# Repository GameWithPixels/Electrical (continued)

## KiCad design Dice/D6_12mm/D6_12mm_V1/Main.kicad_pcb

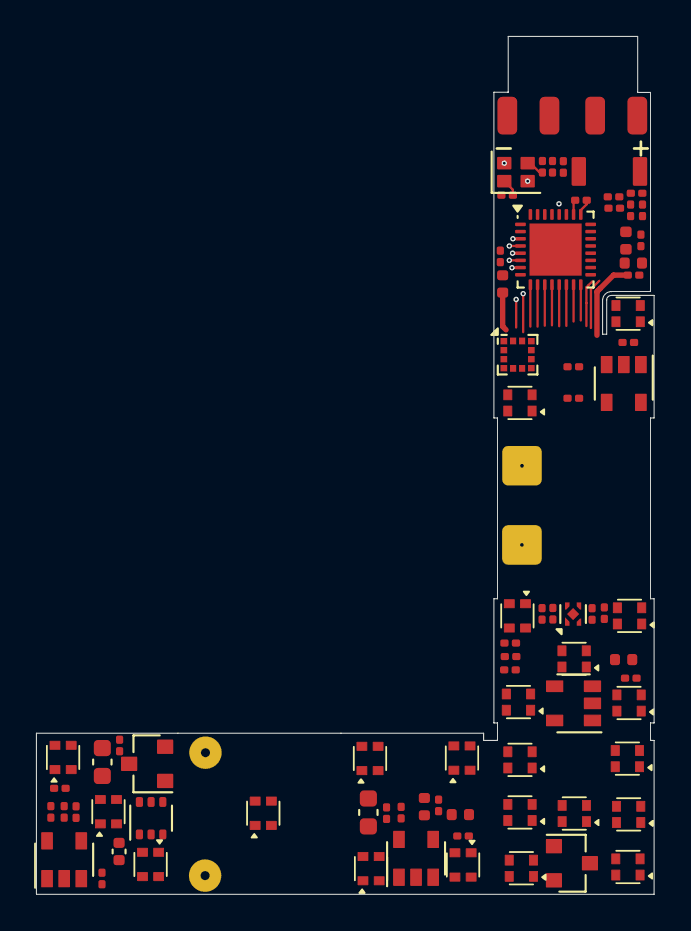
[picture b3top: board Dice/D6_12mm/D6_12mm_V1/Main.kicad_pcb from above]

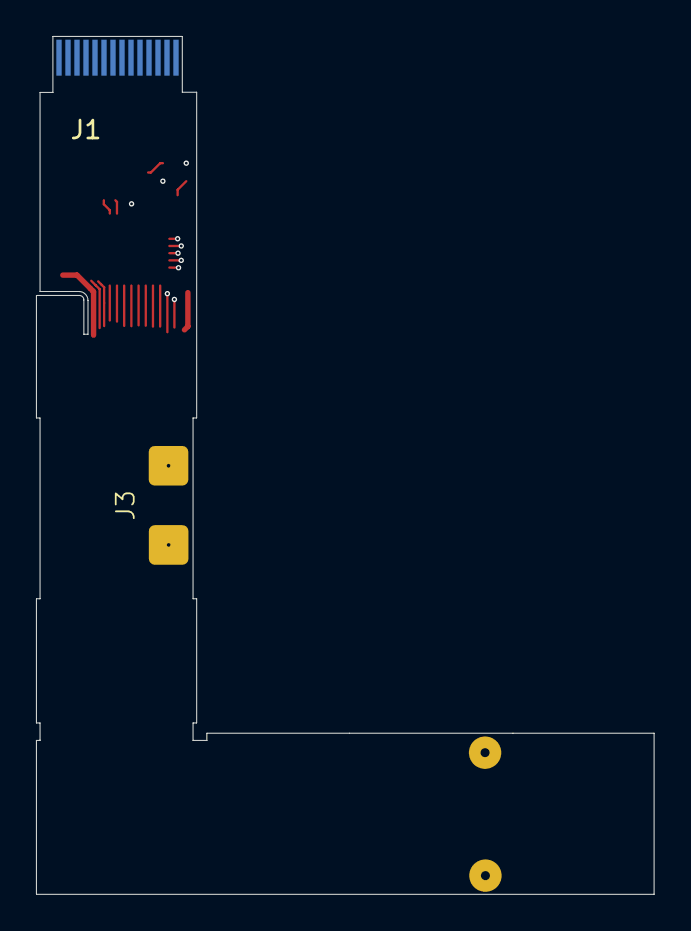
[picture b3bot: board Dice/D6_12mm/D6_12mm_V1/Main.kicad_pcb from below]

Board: 2 copper layers, 34.3 x 47.7 mm, 82 parts (2 on the bottom side), 57 nets.

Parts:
AE1: Antenna_Chip; CHIP_ANT
C1, C9, C10, C18, C29: 4.7uF 10V 20%; C_0402_1005Metric
C2, C5: 12pF 10V 10%; C_0201_0603Metric
C3, C6, C7, C20, C23, C24, C25: 0.1uF 10V 20%; C_0201_0603Metric
C4, C11, C12: DNP; C_0201_0603Metric
C8: 1.2pF 10V 5% C0G; C_0201_0603Metric
C13: 4.7uF 25V 20%; C_0402_1005Metric
C14, C17: 1nF 25V 5% NP0; C_0201_0603Metric
C15: 22uF 10V 20%; C_0603_1608Metric
C19: 10nF 50V 5% NP0; C_0603_1608Metric
C21, C22: 10nF 25V 10%; C_0201_0603Metric
C26, C27, C28: 1.0uF 6.3V 20%; C_0201_0603Metric
D1: BAV99S; SOT-363_SC-70-6
D2, D3, D4, D5, D6, D7, D8, D9, D10, D11, D12, D13, D14, D15, D16, D17, D18, D19, D20, D21, D22, D23: TX1812MWCA5-F01
J1: Conn_01x14; FPC_14
J2: Conn_01x04; FPC-POGO-4
J3: Conn_01x02; Hongjie 10100 Solder Tabs
L1: 2.2uH 10mA 20%; L_0402_1005Metric
L3: 0 Ohm; L_0201_0603Metric
L5: 1.6nH 5%; L_0201_0603Metric
P5: COILA; TestPoint_THTPad_D1.5mm_Drill0.7mm_nosilk
P6: COILB; TestPoint_THTPad_D1.5mm_Drill0.7mm_nosilk
R1, R2, R7: 3.9M 1%; R_0201_0603Metric
R3, R6: R_0201_0603Metric
R4: 10k 1%; R_0201_0603Metric
R8: 10M 1%; R_0201_0603Metric
R9: 100k 1%; R_0201_0603Metric
R10, R11: 3.9k 1%; R_0201_0603Metric
R12: 510R 1%; R_0201_0603Metric
TH1: NTC 100k @ 25C; R_0201_0603Metric
U1: CMT4531; QFN-32-1EP_4x4mm_P0.4mm_EP2.9x2.9mm
U2: SC7A20HTR; LGA-12_2x2mm_P0.5mm
U3: MG78L05AT3; SOT-23
U4: 24C02S(XBLW); SOT-23-5
U5: MT9700; SOT-23-5
U6: ME6212C30M5G; SOT-23-5
U7: DS6101; UDFN-4-1EP_1x1mm_P0.65mm_EP0.48x0.48mm
U8: MGH303A1T3; SOT-23
U9: TP4054(LX); SOT-23-5
Y1: 32MHz 40ppm; Crystal_SMD_2016-4Pin_2.0x1.6mm

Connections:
+5V: C15.1, R1.1, R4.1, U3.1 (VOUT), U9.4 (VCC)
+BATT: C9.1, J3.1, R7.1, R12.1, U5.5 (VIN), U6.1 (VIN), U8.1 (VDD), U9.3 (BAT)
/ACC_INT: U1.13 (PB3), U2.5 (INT1)
/ANTENNA: AE1.1 (FEED), C11.1, L3.2
/ANT_50: C8.1, C12.1, L3.1
/LED_DATA: D2.3 (DIN), U1.4 (PB0)
/LED_RETURN: D23.1 (DOUT), U1.7 (PA6)
/SCL: R10.2, U1.17 (PB7), U2.12 (SCL), U4.1 (SCL)
/SDA: R11.2, U1.16 (PB6), U2.2 (SDA), U4.3 (SDA)
/Wireless Charging/B-: C23.2, J3.2, U7.2 (VSS), U7.5 (PAD)
/Wireless Charging/COILA: C14.1, C17.1, C19.1, D1.3 (K1A2), P5.1
/Wireless Charging/COILB: C14.2, C17.2, C19.2, D1.6 (K3A4), P6.1
/Wireless Charging/COIL_SENSE: C21.1, R1.2, R2.2, U1.9 (PB8)
/Wireless Charging/LED_EN_OUT: U1.12 (PB2), U5.4 (EN)
/Wireless Charging/PROG: R6.1, U1.15 (PB5), U9.5 (PROG)
/Wireless Charging/SM: U1.14 (PB4), U7.3 (SM)
/Wireless Charging/STAT: U1.11 (PB1), U9.1 (CHRG)
/Wireless Charging/TH1: R9.2, TH1.1, U1.18 (PB10)
/Wireless Charging/VBAT_SENSE: C22.1, R7.2, R8.1, U1.10 (PB9)
GND: C1.2, C2.1, C3.2, C4.2, C5.1, C6.2, C7.2, C9.2, C10.2, C11.2, C12.2, C13.2, C15.2, C18.2, C20.2, C21.2, C22.2, C24.2, C25.2, C26.2, C27.2, C28.2, C29.2, D1.1 (A1), D1.4 (A3), D2.2 (GND), D3.2 (GND), D4.2 (GND), D5.2 (GND), D6.2 (GND), D7.2 (GND), D8.2 (GND), D9.2 (GND), D10.2 (GND), D11.2 (GND), D12.2 (GND), D13.2 (GND), D14.2 (GND), D15.2 (GND), D16.2 (GND), D17.2 (GND), D18.2 (GND), D19.2 (GND), D20.2 (GND), D21.2 (GND), D22.2 (GND), D23.2 (GND), J1.3, J1.4, J1.7, J1.8, J2.4, R2.1, R3.2, R4.2, R6.2, R8.2, TH1.2, U1.33 (GND), U2.4 (NC), U2.8 (GND), U2.9 (GND), U3.3 (VSS), U4.2 (GND), U5.2 (GND), U6.2 (VSS), U7.4 (EB-), U8.3 (GND), U9.2 (GND), Y1.2, Y1.4
unnamed: D2.1 (DOUT), D3.3 (DIN)
unnamed: D3.1 (DOUT), D4.3 (DIN)
unnamed: D4.1 (DOUT), D5.3 (DIN)
unnamed: D5.1 (DOUT), D6.3 (DIN)
unnamed: D6.1 (DOUT), D7.3 (DIN)
unnamed: D7.1 (DOUT), D8.3 (DIN)
unnamed: D8.1 (DOUT), D9.3 (DIN)
unnamed: D9.1 (DOUT), D10.3 (DIN)
unnamed: D10.1 (DOUT), D11.3 (DIN)
unnamed: D11.1 (DOUT), D12.3 (DIN)
unnamed: D12.1 (DOUT), D13.3 (DIN)
unnamed: D13.1 (DOUT), D14.3 (DIN)
unnamed: D14.1 (DOUT), D15.3 (DIN)
unnamed: D15.1 (DOUT), D16.3 (DIN)
unnamed: D16.1 (DOUT), D17.3 (DIN)
unnamed: D17.1 (DOUT), D18.3 (DIN)
unnamed: D18.1 (DOUT), D19.3 (DIN)
unnamed: D19.1 (DOUT), D20.3 (DIN)
unnamed: D20.1 (DOUT), D21.3 (DIN)
unnamed: D21.1 (DOUT), D22.3 (DIN)
unnamed: D22.1 (DOUT), D23.3 (DIN)
unnamed: C4.1, C8.2, L5.2, U1.25 (RFIOP)
unnamed: L1.2, U1.23 (SWITCH)
unnamed: C26.1, C27.1, L1.1, U1.24 (VDCDC), U1.27 (VDCDCRF)
unnamed: C1.1, C3.1, U1.8 (VDD_FLASH)
unnamed: L5.1, U1.26 (VDD_PA)
unnamed: C5.2, U1.29 (XO32MM_OUT), Y1.3
unnamed: C2.2, U1.30 (XO32MP_IN), Y1.1
unnamed: R3.1, U5.3 (SET)
unnamed: U6.3 (CE), U8.2 (OUT)
unnamed: C23.1, R12.2, U7.1 (BAT)
RESET: J1.9, U1.3 (RESET)
SWDCLK: J1.6, J2.3, U1.5 (SWDCLK)
SWDIO: J1.5, J2.2, U1.6 (SWDIO)
VDC: C6.1, C10.1, C20.1, C24.1, C25.1, D2.4 (VCC), D3.4 (VCC), D4.4 (VCC), D5.4 (VCC), D6.4 (VCC), D7.4 (VCC), D8.4 (VCC), D9.4 (VCC), D10.4 (VCC), D11.4 (VCC), D12.4 (VCC), D13.4 (VCC), D14.4 (VCC), D15.4 (VCC), D16.4 (VCC), D17.4 (VCC), D18.4 (VCC), D19.4 (VCC), D20.4 (VCC), D21.4 (VCC), D22.4 (VCC), D23.4 (VCC), R9.1, U5.1 (VOUT)
VDD: C7.1, C18.1, C28.1, C29.1, J1.13, J1.14, J2.1, R10.1, R11.1, U1.22 (VCC), U1.28 (VCCRF), U2.3 (IO_VDD), U2.7 (VDD), U4.4 (VCC), U6.5 (VOUT)
VEE: C13.1, D1.2 (K2), D1.5 (K4), U3.2 (VIN)

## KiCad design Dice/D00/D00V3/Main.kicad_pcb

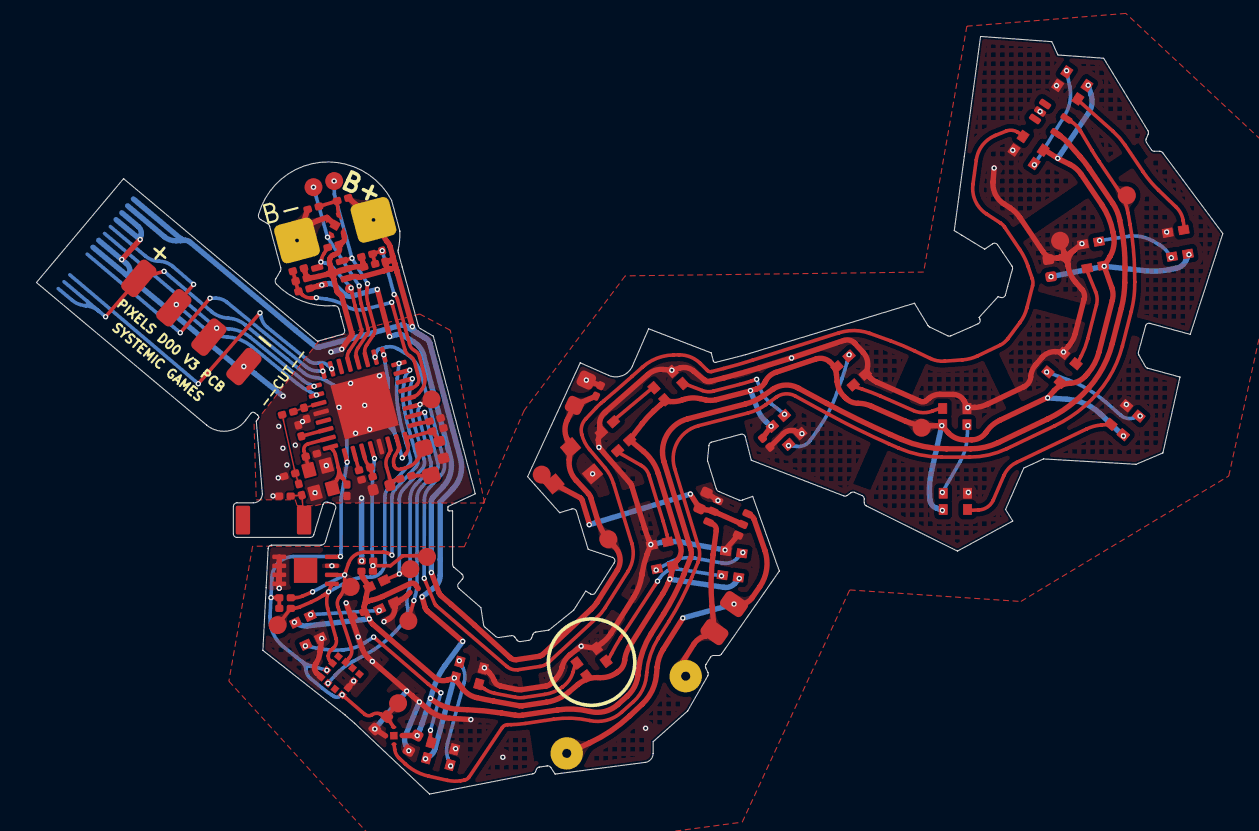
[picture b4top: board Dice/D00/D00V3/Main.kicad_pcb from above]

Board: 2 copper layers, 65.9 x 42.1 mm, 89 parts (1 on the bottom side), 57 nets.

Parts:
AE1: Antenna_Chip; CHIP_ANT
C1, C4, C18: 4.7uF 10V 20%; C_0402_1005Metric
C2, C5: 8pF 10V 10%; C_0201_0603Metric
C3, C6, C10, C14, C23: 0.1uF 10V 20%; C_0201_0603Metric
C7: 100pF NP0 10V 2%; C_0201_0603Metric
C8: 0.8pF 10V 5% C0G; C_0201_0603Metric
C9, C16: 10uF 6.3V 20%; C_0402_1005Metric
C11, C12: DNP; C_0201_0603Metric
C13: 4.7uF 25V 20%; C_0402_1005Metric
C15: 22uF 10V 20%; C_0603_1608Metric
C19: 12nF 50V 5% NP0; C_0805_2012Metric
C21, C22: 10nF 25V 10%; C_0201_0603Metric
D1: BAV99S; SOT-363_SC-70-6
D2, D3, D4, D5, D6, D7, D8, D9, D10, D11, D12, D13, D14, D15, D16, D17, D18, D19, D20: TX1812MWCA5-F01
J1: Conn_01x14; FPC_14
J2: Conn_01x04; FPC-POGO-4
J3: Conn_01x02; Hongjie 10100 Solder Tabs
L1: 10uH 100mA 20%; L_0603_1608Metric
L2: 15nH 100mA 5%; L_0201_0603Metric
L3: 0 Ohm; R_0201_0603Metric
L5: 3.9nH 5%; L_0201_0603Metric
P5: COILA; TestPoint_THTPad_D1.5mm_Drill0.7mm_nosilk
P6: COILB; TestPoint_THTPad_D1.5mm_Drill0.7mm_nosilk
R1, R2, R7: 3.9M 1%; R_0201_0603Metric
R3: 24.3k 1%; R_0201_0603Metric
R4: 10k 1%; R_0201_0603Metric
R5, R9: 100k 1%; R_0201_0603Metric
R6: 3.57k 1%; R_0201_0603Metric
R8: 10M 1%; R_0201_0603Metric
R10, R11: 3.9k 1%; R_0201_0603Metric
R12: 510R 1%; R_0201_0603Metric
TH1: NTC 100k @ 25C; R_0201_0603Metric
U1: N52810_QFN32; QFN-32-1EP_5x5mm_P0.5mm_EP3.1x3.1mm
U2: SC7A20HTR; LGA-12_2x2mm_P0.5mm
U3: PJ75BL50SA; SOT-23
U4: ME6230; FPB1_1-4
U5: BL24C02F-NTRC; TDFN-8-1EP_3x2mm_P0.5mm_EP1.3x1.4mm
U6: AW35122
U7: DS6101; UDFN-4-1EP_1x1mm_P0.65mm_EP0.48x0.48mm
U8: SL1605; SOT-553
U9: XT4051; SOT-553
W1: LED_DATA1; TEST_PIN
W2: PROG; TEST_PIN
W4: VDC; TEST_PIN
W5: SM; TEST_PIN
W6: MAG1; TEST_PIN
W7: ACC_INT; TEST_PIN
W8: SCL; TEST_PIN
W9: SDA; TEST_PIN
W15: +5V; TEST_PIN
W16: VIN; TEST_PIN
W17: STAT; TEST_PIN
W19: GND; TEST_PIN
W20: TH1; TEST_PIN
W21: LED2; TEST_PIN
W25: VDD; TEST_PIN
Y1: 32MHz 40ppm; Crystal_SMD_2016-4Pin_2.0x1.6mm

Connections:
+5V: C15.1, R1.1, R4.1, U3.2 (VOUT), U9.5 (VCC), W15.1
+BATT: C16.1, J1.1, J1.2, J3.1, R7.1, R12.1, U4.4 (VIN), U6.A2 (VIN), U8.4 (VDD), U9.1 (BAT)
/5V_SENSE: C21.1, R1.2, R2.2, U1.5 (P0.05/AIN3)
/ACC_INT: U1.3 (P0.01/XL2), U2.5 (INT1), W7.1
/ANTENNA: AE1.1 (FEED), C11.1, L3.2
/ANT_50: C12.1, L3.1, L5.2
/ANT_NRF: C8.1, L5.1, U1.19 (ANT)
/BATT_NTC_SENSE: R9.2, TH1.1, U1.28 (P0.30/AIN6), W20.1
/LED_DATA: D2.3 (DIN), U1.6 (P0.06), W1.1
/LED_EN: U1.2 (P0.00/XL1), U6.B2 (EN), W21.1
/LED_RETURN: D20.1 (DOUT), U1.10 (P0.12)
/PROG: R6.1, U1.13 (P0.16/TDATA1), U9.4 (PROG), W2.1
/Power Supply/MAG1_: U4.3 (CE), U8.5 (OUT), W6.1
/SCL: R10.2, U1.7 (P0.09), U2.12 (SCL), U5.6 (SCL), W8.1
/SDA: R11.2, U1.8 (P0.10), U2.2 (SDA), U5.5 (SDA), W9.1
/SM: U1.12 (P0.15), U7.3 (SM), W5.1
/STATS: U1.11 (P0.14), U9.3 (CHRG), W17.1
/VBAT_SENSE: C22.1, R7.2, R8.1, U1.4 (P0.04/AIN2)
/Wireless Charging/B-: C23.2, J3.2, U7.2 (VSS), U7.5 (PAD)
/Wireless Charging/COILA: C19.1, D1.3 (K1A2), P5.1
/Wireless Charging/COILB: C19.2, D1.6 (K3A4), P6.1
GND: C1.2, C2.1, C3.2, C4.2, C5.1, C6.2, C7.2, C8.2, C9.2, C10.2, C11.2, C12.2, C13.2, C14.2, C15.2, C16.2, C18.2, C21.2, C22.2, D1.1 (A1), D1.4 (A3), D2.2 (GND), D3.2 (GND), D4.2 (GND), D5.2 (GND), D6.2 (GND), D7.2 (GND), D8.2 (GND), D9.2 (GND), D10.2 (GND), D11.2 (GND), D12.2 (GND), D13.2 (GND), D14.2 (GND), D15.2 (GND), D16.2 (GND), D17.2 (GND), D18.2 (GND), D19.2 (GND), D20.2 (GND), J1.3, J1.4, J1.7, J1.8, J2.4, R2.1, R3.1, R4.2, R6.2, R8.2, TH1.2, U1.20 (VSS), U1.29 (VSS), U1.33 (VSS), U2.4 (NC), U2.8 (GND), U2.9 (GND), U3.1 (VSS), U4.2 (VSS), U5.1 (A0), U5.2 (A1), U5.3 (A2), U5.4 (GND), U5.7 (WP), U6.B1 (GND), U7.4 (EB-), U8.2 (GND), U9.2 (GND), W19.1, Y1.2, Y1.4
unnamed: D2.1 (DOUT), D3.3 (DIN)
unnamed: D3.1 (DOUT), D4.3 (DIN)
unnamed: D4.1 (DOUT), D5.3 (DIN)
unnamed: D5.1 (DOUT), D6.3 (DIN)
unnamed: D6.1 (DOUT), D7.3 (DIN)
unnamed: D7.1 (DOUT), D8.3 (DIN)
unnamed: D8.1 (DOUT), D9.3 (DIN)
unnamed: D9.1 (DOUT), D10.3 (DIN)
unnamed: D10.1 (DOUT), D11.3 (DIN)
unnamed: D11.1 (DOUT), D12.3 (DIN)
unnamed: D12.1 (DOUT), D13.3 (DIN)
unnamed: D13.1 (DOUT), D14.3 (DIN)
unnamed: D14.1 (DOUT), D15.3 (DIN)
unnamed: D15.1 (DOUT), D16.3 (DIN)
unnamed: D16.1 (DOUT), D17.3 (DIN)
unnamed: D17.1 (DOUT), D18.3 (DIN)
unnamed: D18.1 (DOUT), D19.3 (DIN)
unnamed: D19.1 (DOUT), D20.3 (DIN)
unnamed: L1.2, L2.1
unnamed: L1.1, U1.31 (DCC)
unnamed: C3.1, U1.1 (DEC1)
unnamed: C7.1, U1.22 (DEC3)
unnamed: C1.1, L2.2, U1.30 (DEC4)
unnamed: R5.2, U1.26 (P0.25)
unnamed: R3.2, R5.1, U1.27 (P0.28/AIN4)
unnamed: C5.2, U1.23 (XC1), Y1.3
unnamed: C2.2, U1.24 (XC2), Y1.1
unnamed: C23.1, R12.2, U7.1 (BAT)
RESET: J1.9, U1.16 (P0.16)
SWDCLK: J1.6, J2.3, U1.17 (SWDCLK)
SWDIO: J1.5, J2.2, U1.18 (SWDIO)
TXO: J1.12, U1.15 (P0.20/TCLK)
VDC: C6.1, C9.1, C14.1, D2.4 (VCC), D3.4 (VCC), D4.4 (VCC), D5.4 (VCC), D6.4 (VCC), D7.4 (VCC), D8.4 (VCC), D9.4 (VCC), D10.4 (VCC), D11.4 (VCC), D12.4 (VCC), D13.4 (VCC), D14.4 (VCC), D15.4 (VCC), D16.4 (VCC), D17.4 (VCC), D18.4 (VCC), D19.4 (VCC), D20.4 (VCC), R9.1, U6.A1 (VOUT), W4.1
VDD: C4.1, C10.1, C18.1, J1.13, J1.14, J2.1, R10.1, R11.1, U1.9 (VDD), U1.25 (VDD), U1.32 (VDD), U2.3 (IO_VDD), U2.7 (VDD), U4.1 (VOUT), U5.8 (VCC), W25.1
VEE: C13.1, D1.2 (K2), D1.5 (K4), U3.3 (VIN), W16.1

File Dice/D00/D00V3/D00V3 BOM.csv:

"Reference","Qty","Value","DNP","Footprint","Manufacturer","Part Number"
"AE1","1","Antenna_Chip","","Pixels-dice:CHIP_ANT","Microgate","MGMA3216H2450-A02"
"C1,C4,C18","3","4.7uF 10V 20%","","Pixels-dice:C_0402_1005Metric","HRE","CGA0402X5R475M100GT"
"C2,C5","2","8pF 10V 10%","","Capacitor_SMD:C_0201_0603Metric","HRE","CGA0201C0G8R0B250ET"
"C3,C6,C10,C14,C23","5","0.1uF 10V 20%","","Capacitor_SMD:C_0201_0603Metric","HRE","CGA0201X5R104K100ET"
"C7","1","100pF NP0 10V 2%","","Capacitor_SMD:C_0201_0603Metric","HRE","CGA0201C0G101J500ET"
"C8","1","0.8pF 10V 5% C0G","","Capacitor_SMD:C_0201_0603Metric","HRE","CGA0201C0GR80C250ET"
"C9,C16","2","10uF 6.3V 20%","","Pixels-dice:C_0402_1005Metric","HRE","CGA0402X5R106M6R3GT"
"C13","1","4.7uF 25V 20%","","Capacitor_SMD:C_0402_1005Metric","HRE","CGA0402X5R475M250GT"
"C15","1","22uF 10V 20%","","Capacitor_SMD:C_0603_1608Metric","HRE","CGA0603X5R226M100JT"
"C19","1","12nF 50V 5% NP0","","Capacitor_SMD:C_0805_2012Metric","Murata","GRM2195C1H123JA01D"
"C21,C22","2","10nF 25V 10%","","Capacitor_SMD:C_0201_0603Metric","HRE","CGA0201X5R103K250ET"
"D1","1","BAV99S","","Pixels-dice:SOT-363_SC-70-6","Nexperia","BAV99S,115"
"D2,D3,D4,D5,D6,D7,D8,D9,D10,D11,D12,D13,D14,D15,D16,D17,D18,D19,D20","19","TX1812MWCA5-F01","","Pixels-dice:TX1812MWCA5-F01","TCWIN","TX1812MWCA5-F01"
"L1","1","10uH 100mA 20%","","Inductor_SMD:L_0603_1608Metric","FH","CMI160808J100KT"
"L2","1","15nH 100mA 5%","","Inductor_SMD:L_0201_0603Metric","FH","VHF060303HQ15NKT"
"L3","1","0 Ohm","","Resistor_SMD:R_0201_0603Metric","UNI-ROYAL(Uniroyal Elec)","0201WMF0000TEE"
"L5","1","3.9nH 5%","","Inductor_SMD:L_0201_0603Metric","FH"," VHF060303HQ3N9ST02"
"R1,R2,R7","3","3.9M 1%","","Resistor_SMD:R_0201_0603Metric","UNI-ROYAL(Uniroyal Elec)","0201WMF3904TEE"
"R3","1","24.3k 1%","","Resistor_SMD:R_0201_0603Metric","UNI-ROYAL(Uniroyal Elec)","0201WMF2432TEE"
"R4","1","10k 1%","","Resistor_SMD:R_0201_0603Metric","UNI-ROYAL(Uniroyal Elec)","0201WMF1002TEE"
"R5,R9","2","100k 1%","","Resistor_SMD:R_0201_0603Metric","UNI-ROYAL(Uniroyal Elec)","0201WMF1003TEE"
"R6","1","3.57k 1%","","Resistor_SMD:R_0201_0603Metric","UNI-ROYAL(Uniroyal Elec)","0201WMF3571TEE"
"R8","1","10M 1%","","Resistor_SMD:R_0201_0603Metric","UNI-ROYAL(Uniroyal Elec)","0201WMF1005TEE"
"R10,R11","2","3.9k 1%","","Resistor_SMD:R_0201_0603Metric","UNI-ROYAL(Uniroyal Elec)","0201WMF3651TEE"
"R12","1","510R 1%","","Resistor_SMD:R_0201_0603Metric","UNI-ROYAL(Uniroyal Elec)","NQ01WMJ0511TEE"
"TH1","1","NTC 100k @ 25C","","Resistor_SMD:R_0201_0603Metric","muRata ","NCP03WF104F05RL "
"U1","1","N52810_QFN32","","Pixels-dice:QFN-32-1EP_5x5mm_P0.5mm_EP3.1x3.1mm","Nordic Semiconductor","NRF52810-QCAA-R"
"U2","1","SC7A20HTR","","Package_LGA:LGA-12_2x2mm_P0.5mm","Hangzhou Silan Microelectronics","SC7A20HTR"
"U3","1","PJ75BL50SA","","Pixels-dice:SOT-23","PJSEMI","PJ75BL50SA"
"U4","1","ME6230","","Pixels-dice:FPB1_1-4","MICRONE(Nanjing Micro One Elec)","ME6230C30U4AG"
"U5","1","BL24C02F-NTRC","","Pixels-dice:TDFN-8-1EP_3x2mm_P0.5mm_EP1.3x1.4mm","","BL24C02F-NTRC"
"U6","1","AW35122","","Pixels-dice:AW35122","AWINIC(Shanghai Awinic Tech)","AW35122FDR"
"U7","1","DS6101","","Package_DFN_QFN:UDFN-4-1EP_1x1mm_P0.65mm_EP0.48x0.48mm","DSTECH"," DS6101AED4"
"U8","1","SL1605","","Package_TO_SOT_SMD:SOT-553","Slkor(SLKORMICRO Elec.)","SL1605TL"
"U9","1","XT4051","","Package_TO_SOT_SMD:SOT-553","NATLINEAR","XT4051K421KR-G"
"Y1","1","32MHz 40ppm","","Pixels-dice:Crystal_SMD_2016-4Pin_2.0x1.6mm","TOGNJING","XTM20032000DT00351001"

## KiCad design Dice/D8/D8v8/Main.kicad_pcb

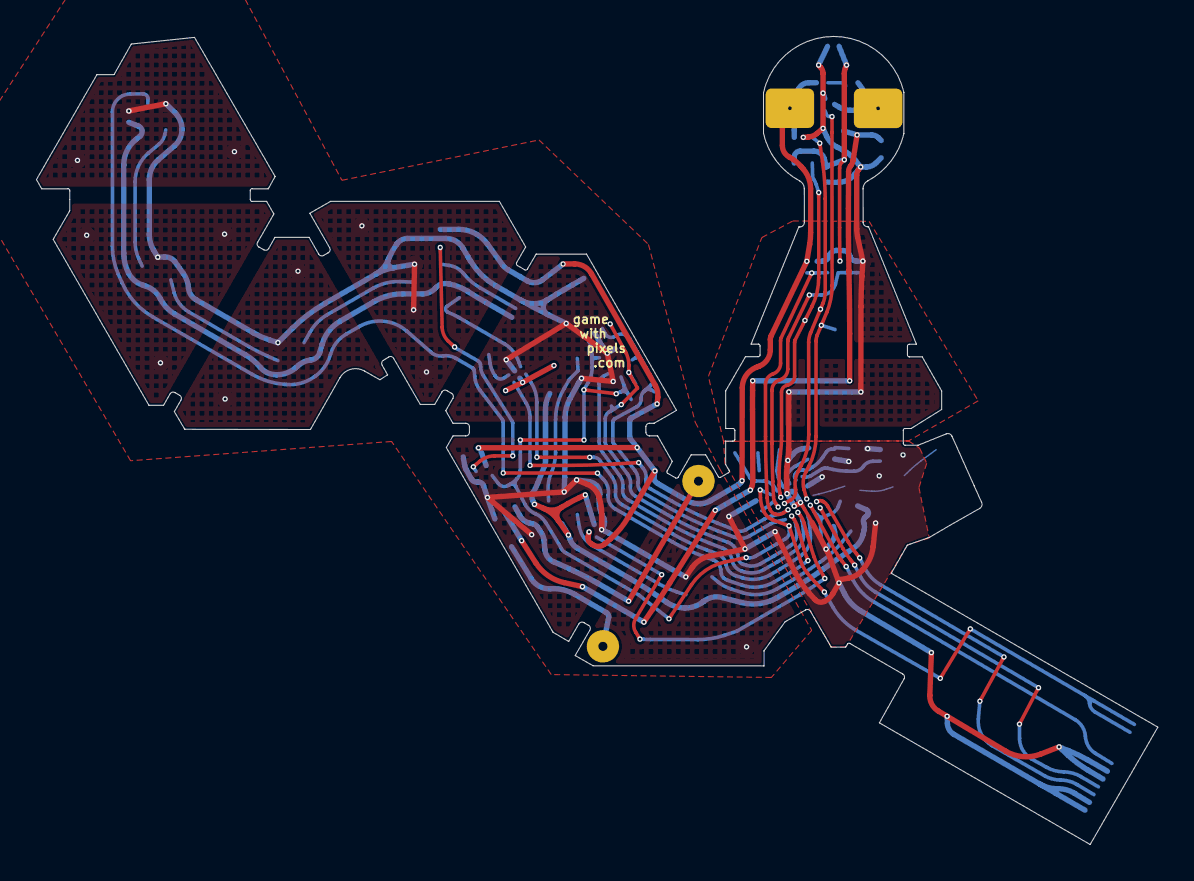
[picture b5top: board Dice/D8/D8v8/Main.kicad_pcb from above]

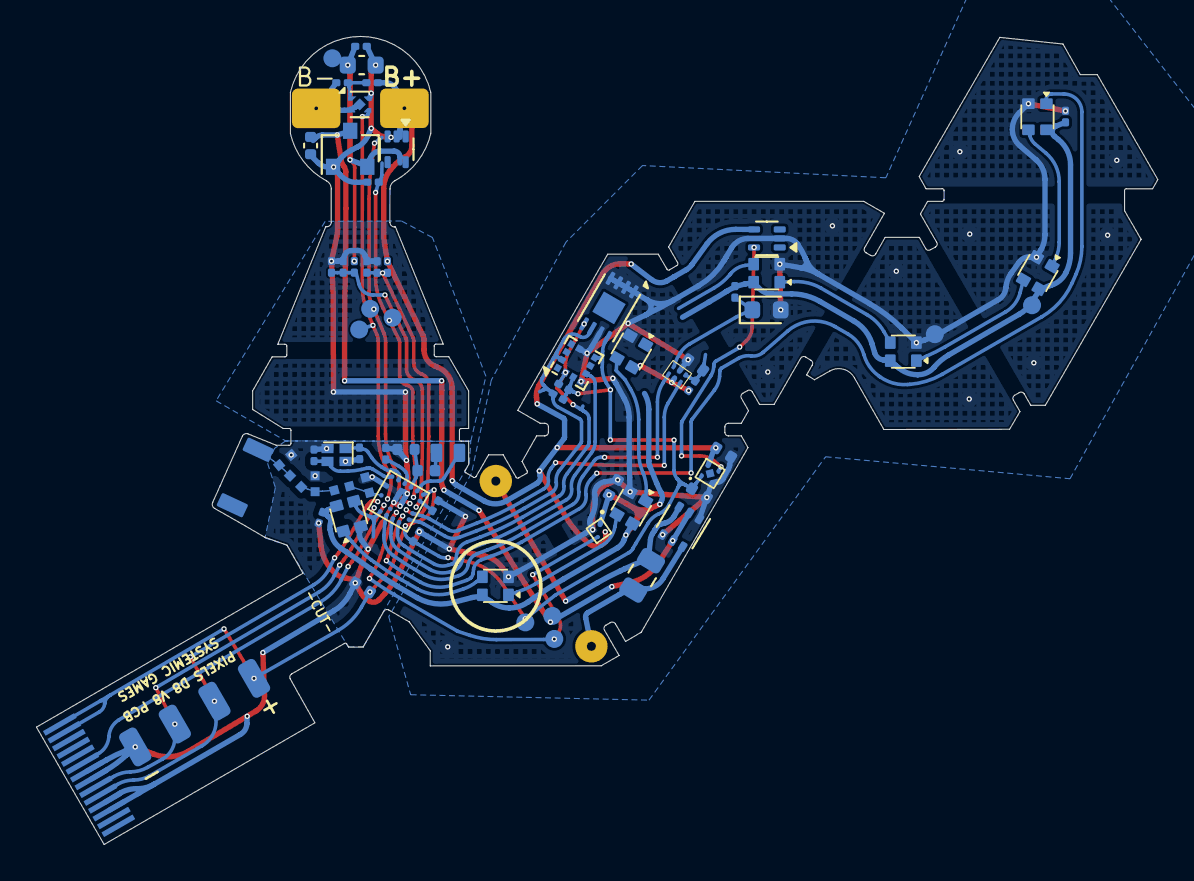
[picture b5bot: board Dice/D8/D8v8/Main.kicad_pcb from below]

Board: 2 copper layers, 62.3 x 44.9 mm, 73 parts (73 on the bottom side), 46 nets.

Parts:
AE1: Antenna_Chip; CHIP_ANT
C1, C4, C18: 4.7uF 10V 20%; C_0402_1005Metric
C2, C5: 8pF 10V 10%; C_0201_0603Metric
C3, C6, C10, C14, C23: 0.1uF 10V 20%; C_0201_0603Metric
C7: 100pF NP0 10V 2%; C_0201_0603Metric
C8: 0.8pF 10V 5% C0G; 0402_RF
C9, C16: 10uF 6.3V 20%; C_0402_1005Metric
C11, C12: DNP; 0402_RF
C13: 4.7uF 25V 20%; C_0402_1005Metric
C15: 22uF 10V 20%; C_0603_1608Metric
C19: 12nF 50V 5% NP0; C_0805_2012Metric
C21, C22: 10nF 25V 10%; C_0201_0603Metric
D1: BAV99S; SOT-363_SC-70-6
D2, D3, D4, D5, D6, D7, D8, D9: TX1812MWCA5-F01
J1: Conn_01x14; FPC_14
J2: Conn_01x04; FPC-POGO-4
J3: Conn_01x02; Hongjie 10100 Solder Tabs
L1: 10uH 100mA 20%; C_1.2x1.8
L2: 15nH 100mA 5%; L_0402_1005Metric
L3: 0 Ohm; 0402_RF
L5: 3.9nH 5%; 0402_RF
P5: COILA; TestPoint_THTPad_D1.5mm_Drill0.7mm_nosilk
P6: COILB; TestPoint_THTPad_D1.5mm_Drill0.7mm_nosilk
Q1: ZSPT-Z1608C-06F-Z4; D_0603_1608Metric
R1, R2, R7: 3.9M 1%; R_0201_0603Metric
R4, R5: 10k 1%; R_0201_0603Metric
R6, R10, R11: 3.9k 1%; R_0201_0603Metric
R8: 10M 1%; R_0201_0603Metric
R9: 100k 1%; R_0201_0603Metric
R12: 510R 1%; R_0201_0603Metric
TH1: NTC 100k @ 25C; R_0402_1005Metric
U1: NRF52810-CAAA-R; WLCSP
U2: SC7A20HTR; LGA-12_2x2mm_P0.5mm
U3: PJ75BL50SA; SOT-23
U4: ME6230; FPB1_1-4
U5: BL24C02F-NTRC; TDFN-8-1EP_3x2mm_P0.5mm_EP1.3x1.4mm
U6: AW35122
U7: DS6101; UDFN-4-1EP_1x1mm_P0.65mm_EP0.48x0.48mm
U8: SL1605; SOT-553
U9: XT4051; SOT-553
U10: WAS3157D-6/TR; DFN1109-6
W2: PROG; TEST_PIN
W4: VDC; TEST_PIN
W5: SM; TEST_PIN
W15: +5V; TEST_PIN
W16: VIN; TEST_PIN
W17: STAT; TEST_PIN
W19: GND; TEST_PIN
W21: LED2; TEST_PIN
W25: VDD; TEST_PIN
Y1: 32MHz 40ppm; SX16Y032000B81T001

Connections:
+5V: C15.1, R1.1, R4.1, U3.2 (VOUT), U9.5 (VCC), W15.1
+BATT: C16.1, J3.1, R7.1, R12.1, U4.4 (VIN), U6.A2 (VIN), U8.4 (VDD), U9.1 (BAT)
/5V_SENSE: C21.1, R1.2, R2.2, U1.D6 (P0.03/AIN1)
/ACC_INT: U1.G4 (P0.15), U2.5 (INT1)
/ANTENNA: AE1.1 (FEED), C11.1, L3.2
/ANT_50: C12.1, L3.1, L5.2
/ANT_NRF: C8.1, L5.1, U1.E1 (ANT)
/LED_DATA: D2.3 (DIN), U1.G2 (P0.20/TCLK)
/LED_EN: U1.F4 (P0.14), U6.B2 (EN), W21.1
/LED_RETURN: D9.1 (DOUT), U1.F5 (P0.11)
/MAG1_: U4.3 (CE), U8.5 (OUT)
/NTC_PHOTO_SENSE: U1.E6 (P0.05/AIN3), U10.6 (A)
/OPT_A2D: Q1.1 (C), R5.2, U10.3 (B1)
/PROG: R6.1, U1.B5 (P0.00/XL1), U9.4 (PROG), W2.1
/SCL: R10.2, U1.F6 (P0.8), U2.12 (SCL), U5.6 (SCL)
/SDA: R11.2, U1.G5 (P0.12), U2.2 (SDA), U5.5 (SDA)
/SENSE_SELECT: U1.G3 (P0.16/TDATA1), U10.4 (S)
/SM: U1.E2 (P0.18/TDATA0), U7.3 (SM), W5.1
/STATS: U1.D5 (P0.01/XL2), U9.3 (CHRG), W17.1
/VBAT_SENSE: C22.1, R7.2, R8.1, U1.E5 (P0.04/AIN2)
/Wireless Charging/B-: C23.2, J3.2, U7.2 (VSS), U7.5 (PAD)
/Wireless Charging/COILA: C19.1, D1.3 (K1A2), P5.1
/Wireless Charging/COILB: C19.2, D1.6 (K3A4), P6.1
/Wireless Charging/TH1: R9.2, TH1.1, U10.1 (B0)
GND: C1.2, C2.1, C3.2, C4.2, C5.1, C6.2, C7.2, C8.2, C9.2, C10.2, C11.2, C12.2, C13.2, C14.2, C15.2, C16.2, C18.2, C21.2, C22.2, D1.1 (A1), D1.4 (A3), D2.2 (GND), D3.2 (GND), D4.2 (GND), D5.2 (GND), D6.2 (GND), D7.2 (GND), D8.2 (GND), D9.2 (GND), J1.3, J1.4, J1.7, J1.8, J2.4, Q1.2 (E), R2.1, R4.2, R6.2, R8.2, TH1.2, U1.B3 (VSS), U1.B4 (VSS), U1.C1 (VSS_PA), U1.D3 (VSS), U1.D4 (VSS), U1.E3 (VSS), U1.E4 (VSS), U2.4 (NC), U2.8 (GND), U2.9 (GND), U3.1 (VSS), U4.2 (VSS), U5.1 (A0), U5.2 (A1), U5.3 (A2), U5.4 (GND), U5.7 (WP), U6.B1 (GND), U7.4 (EB-), U8.2 (GND), U9.2 (GND), U10.2 (GND), W19.1, Y1.2, Y1.4
unnamed: D2.1 (DOUT), D3.3 (DIN)
unnamed: D3.1 (DOUT), D4.3 (DIN)
unnamed: D4.1 (DOUT), D5.3 (DIN)
unnamed: D5.1 (DOUT), D6.3 (DIN)
unnamed: D6.1 (DOUT), D7.3 (DIN)
unnamed: D7.1 (DOUT), D8.3 (DIN)
unnamed: D8.1 (DOUT), D9.3 (DIN)
unnamed: L1.2, L2.1
unnamed: L1.1, U1.A5 (DCC)
unnamed: C3.1, U1.B6 (DEC1)
unnamed: C7.1, U1.A3 (DEC2)
unnamed: C1.1, L2.2, U1.A4 (DEC4)
unnamed: C5.2, U1.A1 (XC1), Y1.3
unnamed: C2.2, U1.A2 (XC2), Y1.1
unnamed: C23.1, R12.2, U7.1 (BAT)
RESET: J1.9, U1.F2 (P0.21)
SWDCLK: J1.6, J2.3, U1.G1 (SWDCLK)
SWDIO: J1.5, J2.2, U1.F1 (SWDIO)
VDC: C6.1, C9.1, C14.1, D2.4 (VCC), D3.4 (VCC), D4.4 (VCC), D5.4 (VCC), D6.4 (VCC), D7.4 (VCC), D8.4 (VCC), D9.4 (VCC), R5.1, R9.1, U6.A1 (VOUT), U10.5 (VCC), W4.1
VDD: C4.1, C10.1, C18.1, J1.13, J1.14, J2.1, R10.1, R11.1, U1.A6 (VDD), U1.G6 (VDD), U2.3 (IO_VDD), U2.7 (VDD), U4.1 (VOUT), U5.8 (VCC), W25.1
VEE: C13.1, D1.2 (K2), D1.5 (K4), U3.3 (VIN), W16.1

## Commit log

2021-04-27 Initial check in of Dice Kicad files.
    Refactor symbols and footprint libraries.
2021-04-27 Backlink to CADLAB.io has been added.
2021-04-27 Adding -cache.lib files
2021-04-27 More files that I didn't think were needed
2021-04-28 Add Kicad repo for libraries and footprints as submodules.
2021-04-28 Revert "Add Kicad repo for libraries and footprints as submodules."
    This reverts commit 17738251b0d8b6ec0708b87600f08b594a54333c.
2021-04-28 Manually removing submodules
    Reverting last commit didn't remove submodules
2021-06-22 Updated Kicad files for current D20, Adapter and Charger
2021-06-22 Missing a couple folders in last commit
2021-08-18 Update D20 Board design. Store all Datasheets needed.
2021-12-06 Adding All Kicad board files to github
    Re-adding all board files to github. From now on a new Project is started every time a physical board is made. Before that point, we'll use github to keep track of changes. Gerber files and other fab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
2022-01-31 Added Dice V11 boards and several other projects, including new Charger designs, Adaptor boards and JIGs
2022-02-02 Making note of bodge wires on Pi Hat and Pi Jig
2022-05-01 Upgraded a number of projects to Kicad V6 and added D6, PD6 and D12
2022-05-11 Added D12 PCB Design, and Updated Large Charging Case
2022-05-27 Add DC Jack Footprint
2022-05-27 Adding Multi-charger Jig to repo
2022-05-30 Update dice boards with new battery connector.
2022-06-02 Replace C19 with 33nF model, forgot to modify the schematic earlier.
2022-06-24 Started work on D10 and fixed small mistakes in D6, PD6 and D12
2022-06-24 Charger V13 Updates
2022-07-15 Added D10, D00 and D8, D20V12 updates
2022-07-20 More Cleanup of Dice Boards
2022-07-21 D20V12 Finishing Touches and D20V12 RF Version
2022-08-13 Updating D8 and D10 boards, new antenna, etc...
2022-08-22 D20V13 and D20V13 RF Testboard 1. Also tweaks to LCCV2
2022-09-02 Large Charging Case V2 Outline and Keepout zones.
2022-09-04 Updates to D20V13, D6V3 and removing kicad_prl from git
2022-09-27 D20V13 updates
2022-09-27 D6V3 and PD6V2 updates
2022-09-27 Library and Footprint updates
2022-10-17 Commiting WangQing's new layout.
2022-10-17 Better RF Path and edge component placements
2022-10-24 LCCV2 Update from Wang Qing and Me. Moved connector, improved antenna layout.
2022-10-24 Didn't mean to add rar file
2022-11-09 Added D20V14, Update D6 to V3, PD6 to V2 and LCCV2
2022-11-09 Adding Gerber Zip files for D6 and PD6
2022-11-23 Charger V14, D20V15
2022-11-27 Update D20V15 to include NTC over battery
2022-12-14 Single Charger V14
2022-12-14 Large Charging Case V3.1 and updated footprints and libs
2022-12-21 Updated BOM of D20V15, Added D6V4 and PD6V3
2023-01-02 Updated all remaining boards to match D20V15 (D6, PD6, D8, D10 and D12)
2023-01-28 Update Programming connector library symbol and footprint
2023-01-28 Update BOM part numbers based on availability.
2023-01-28 Updated D6, D8, D10 boards
2023-01-28 Charger V15
2023-02-06 Updated all dice boards with smaller programming connector. Added ChargerV16
2023-02-12 Added new symbol and updated gitignore
2023-02-12 Regenerate Gerbers for remaining dice
2023-02-12 Updating Charger V15 and LCCV3 based on testing
2023-02-13 Updated BOMs
2023-05-19 Added Single Charger V15.2
2023-05-19 Added new version of D6->D12 boards
2023-06-15 D20 V15.1
2023-06-15 Adding WQ's V20 Charger
2023-06-15 Adding Charger V19 and LCC3.4
2023-06-22 New Version of All boards! Better Sticky tape shapes, tweaks to board outline, changed C19 footprint, revert coil pads to through holes. Also updated to Kicad 7.
2023-06-28 Updated all boards based on Wang Qing's feedback. Generated renders of all boards. Updated LCC to Kicad 7.
2023-06-28 Update C6/C19 Part number on all boards
2023-08-09 Update Dice FPC and LCC PCB
2023-08-31 Adding LCC3.5 from Wang Qing
2023-10-01 Update D4-D12 dice fpcs
2023-10-01 LCC V3.6
2023-10-04 Fix silkscreen on d6v7
2023-10-12 LCC3.6 Layout Changes and new reset supervisor chip.
2023-11-02 More board updates
2023-11-05 Tweak FPC shapes a bit. Added LCC Tester Jig
2023-12-11 Updated LCC PCB, updated dice fpc. Moved LCC testing jig
2024-02-02 LCCV3.8 and Jig updates
2024-05-01 Update BOM on all dice. Make sure testpins are excluded from BOM in all dice. Slight Tweak to D8 layout.
2024-05-01 D20V16 with small tweak to LED13 position
2024-05-14 Adding missing LCC3.8 and LCC Adapter
2024-10-26 Super6, LCCV4 updates and Kicad8
2024-11-26 D00V1 and some components and libs + jigs
2024-12-02 D10V5, D20V16 and Super6V1
2024-12-24 D6V9 and new Jigs
2025-03-11 Updated a bunch of boards, added Jogs and 12mm D6 proto
2025-07-05 A bunch of prototype boards
2025-07-29 more board file updates
2025-08-19 Updated boards
2025-09-01 more pcb updates
2025-09-04 Hex Charer V1.3
2025-10-04 Updated FPCs and Hex Charger PCB
2025-10-11 Updated schematic Titles in D20V17 and likes, added 12mm D6 and Charging Jig
2025-10-12 Updated latest FPC versions
2025-10-12 fix glue layer on D8
2025-10-14 small tweaks to fr4 stiffener
2025-10-28 more tweaks to d6_12mm and charging jig
2025-11-27 hex charger jig
2025-11-27 update hex charger
